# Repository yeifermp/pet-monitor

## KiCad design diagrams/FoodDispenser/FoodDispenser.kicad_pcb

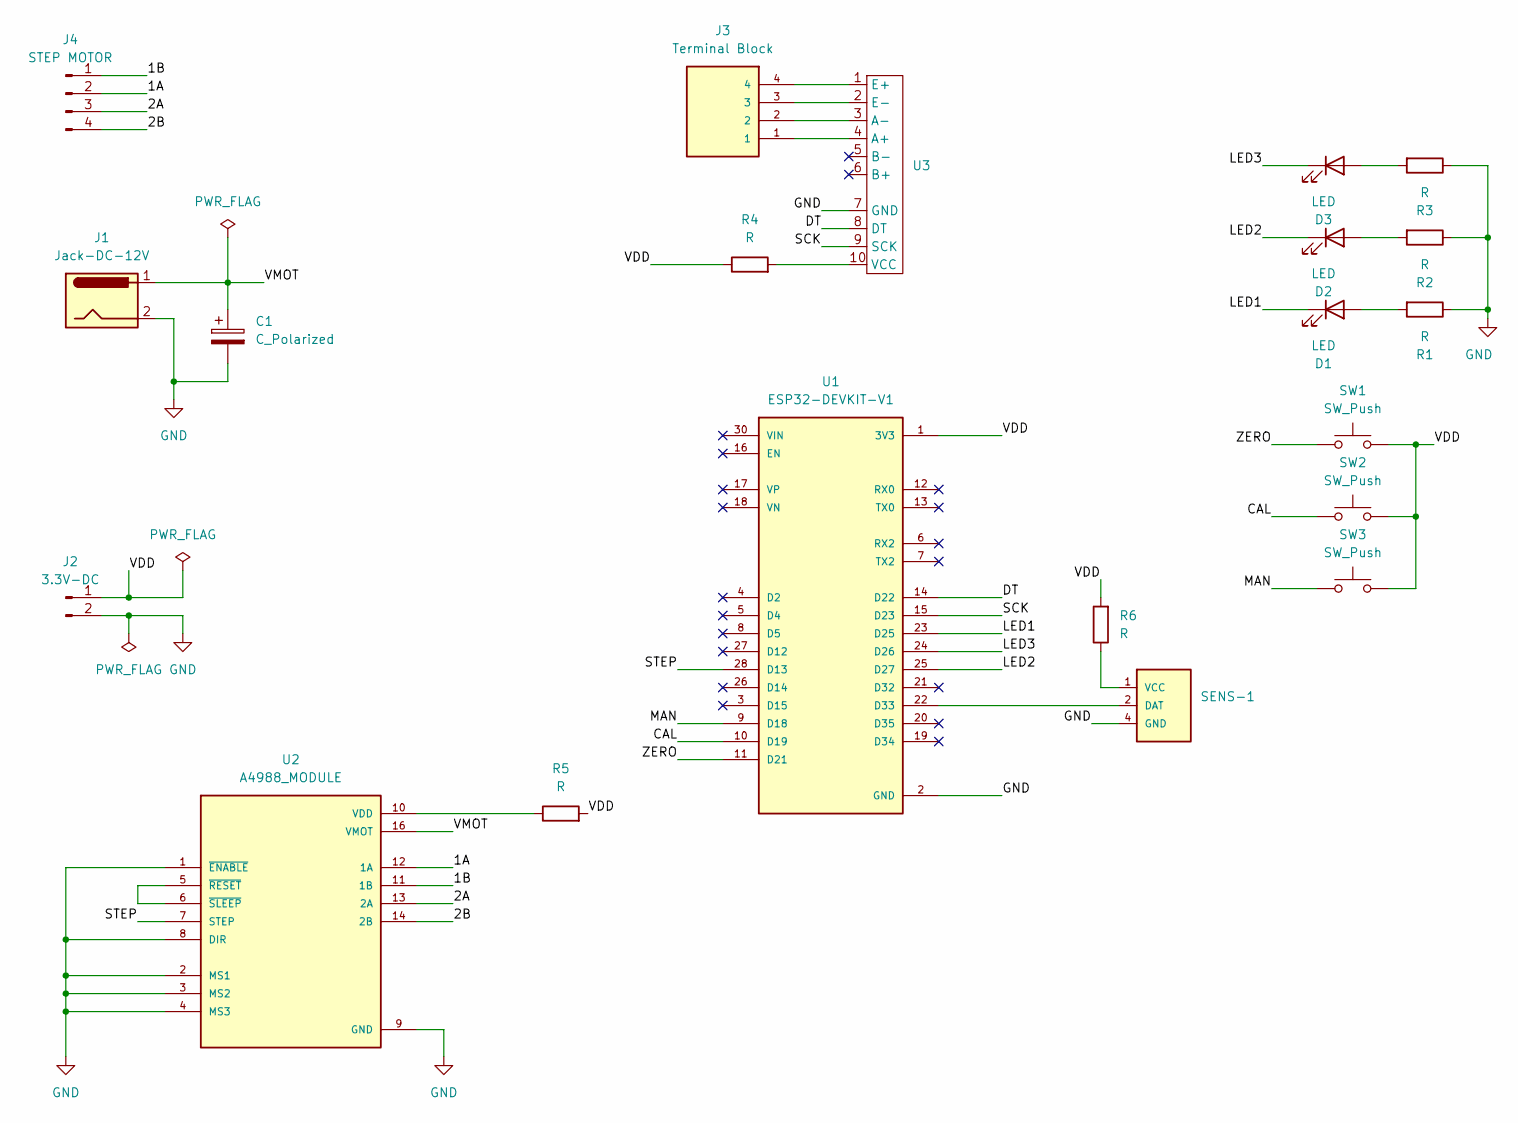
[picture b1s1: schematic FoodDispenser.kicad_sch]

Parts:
C1: C_Polarized; CP_Radial_D6.3mm_P2.50mm
D1, D2, D3: LED; LED_D3.0mm
J1: Jack-DC-12V; BarrelJack_Horizontal
J2: 3.3V-DC; PinHeader_1x02_P2.54mm_Vertical
J3: Terminal Block; Termial_Block_04
J4: STEP MOTOR; PinHeader_1x04_P2.54mm_Vertical
R1, R2, R3: R; R_Axial_DIN0207_L6.3mm_D2.5mm_P7.62mm_Horizontal
R4, R5, R6: R; R_1206_3216Metric_Pad1.30x1.75mm_HandSolder
SENS-1: SENSOR-DHT11
SW1, SW2, SW3: SW_Push; SW_PUSH-12mm
U1: ESP32-DEVKIT-V1; MODULE_ESP32_DEVKIT_V1; PARTREV N/A
U2: A4988_MODULE
U3: HX711-MODULE

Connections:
/1A: J4.2, U2.12 (1A)
/1B: J4.1, U2.11 (1B)
/2A: J4.3, U2.13 (2A)
/2B: J4.4, U2.14 (2B)
/CAL: SW2.1, U1.10 (D19)
/DT: U1.14 (D22), U3.8 (DT)
/LED1: D1.1 (K), U1.23 (D25)
/LED2: D2.1 (K), U1.25 (D27)
/LED3: D3.1 (K), U1.24 (D26)
/MAN: SW3.1, U1.9 (D18)
/SCK: U1.15 (D23), U3.9 (SCK)
/STEP: U1.28 (D13), U2.7 (STEP)
/VDD: J2.1, R4.1, R5.2, R6.2, SW1.2, SW2.2, SW3.2, U1.1 (3V3)
/VMOT: C1.1, J1.1, U2.16 (VMOT)
/ZERO: SW1.1, U1.11 (D21)
GND: C1.2, J1.2, J2.2, R1.1, R2.1, R3.1, SENS-1.4 (GND), U1.2 (GND), U1.29 (GND), U2.1 (~ENABLE), U2.2 (MS1), U2.3 (MS2), U2.4 (MS3), U2.8 (DIR), U2.9 (GND), U2.15 (GND), U3.7 (GND)
unnamed: D1.2 (A), R1.2
unnamed: D2.2 (A), R2.2
unnamed: D3.2 (A), R3.2
unnamed: SENS-1.2 (DAT), U1.22 (D33)
unnamed: R6.1, SENS-1.1 (VCC)
unnamed: R5.1, U2.10 (VDD)
unnamed: U2.5 (~RESET), U2.6 (~SLEEP)
unnamed: J3.1, U3.4 (A+)
unnamed: J3.2, U3.3 (A-)
unnamed: J3.4, U3.1 (E+)
unnamed: J3.3, U3.2 (E-)
unnamed: R4.2, U3.10 (VCC)

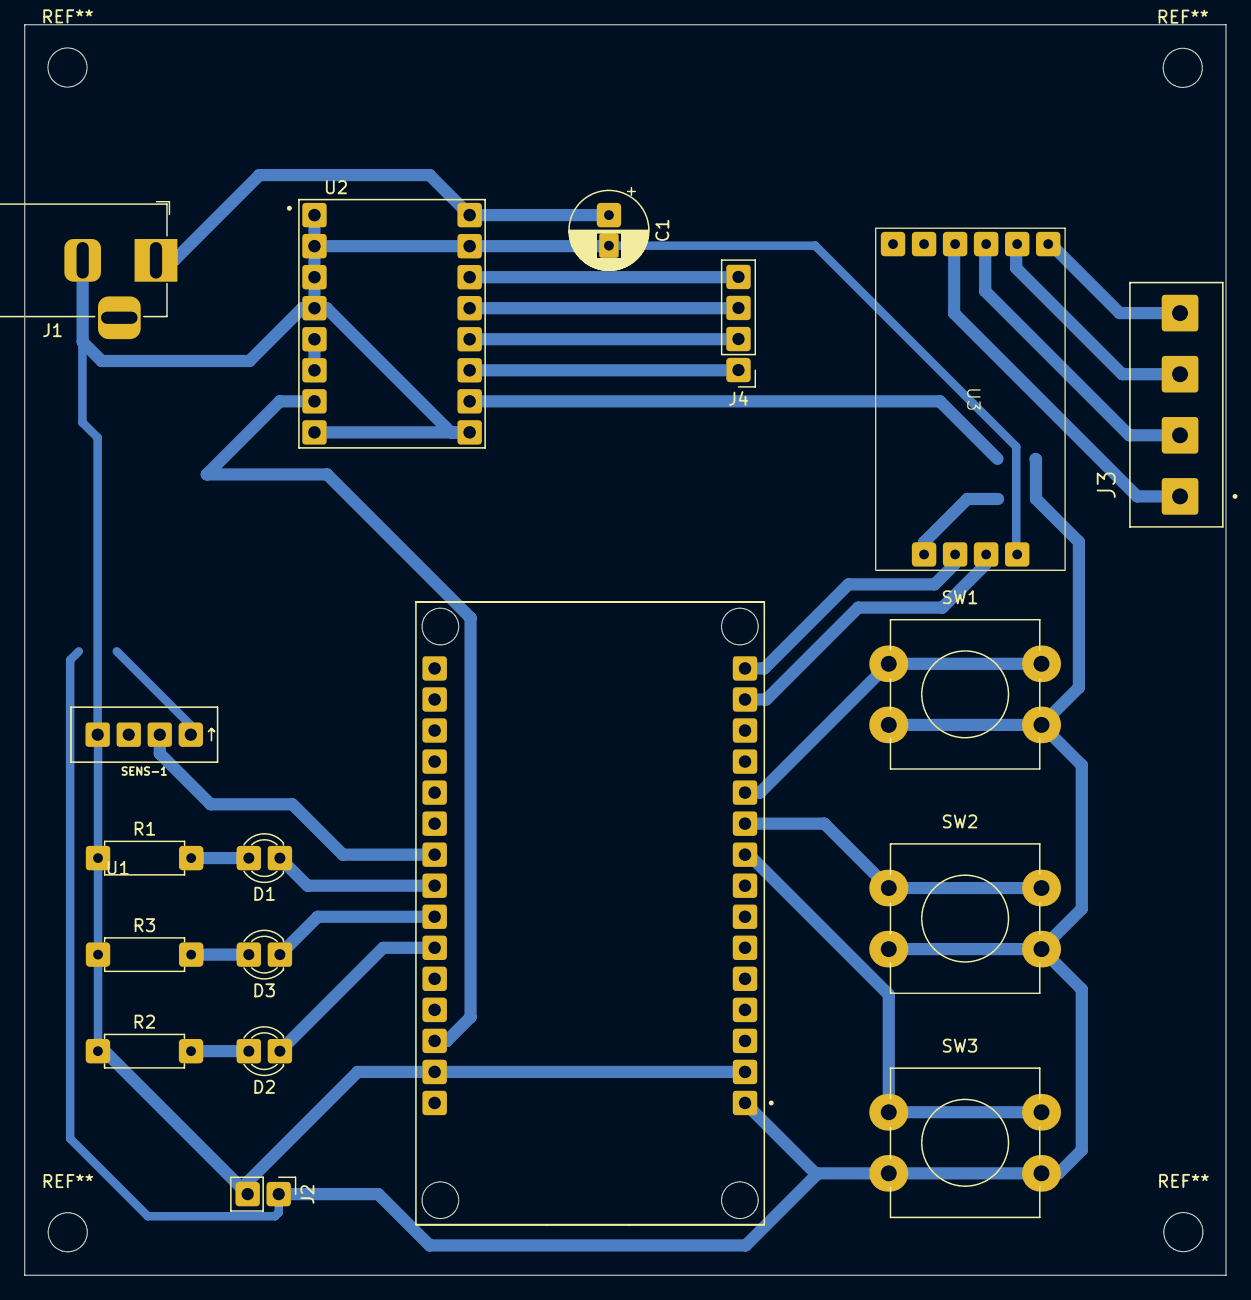
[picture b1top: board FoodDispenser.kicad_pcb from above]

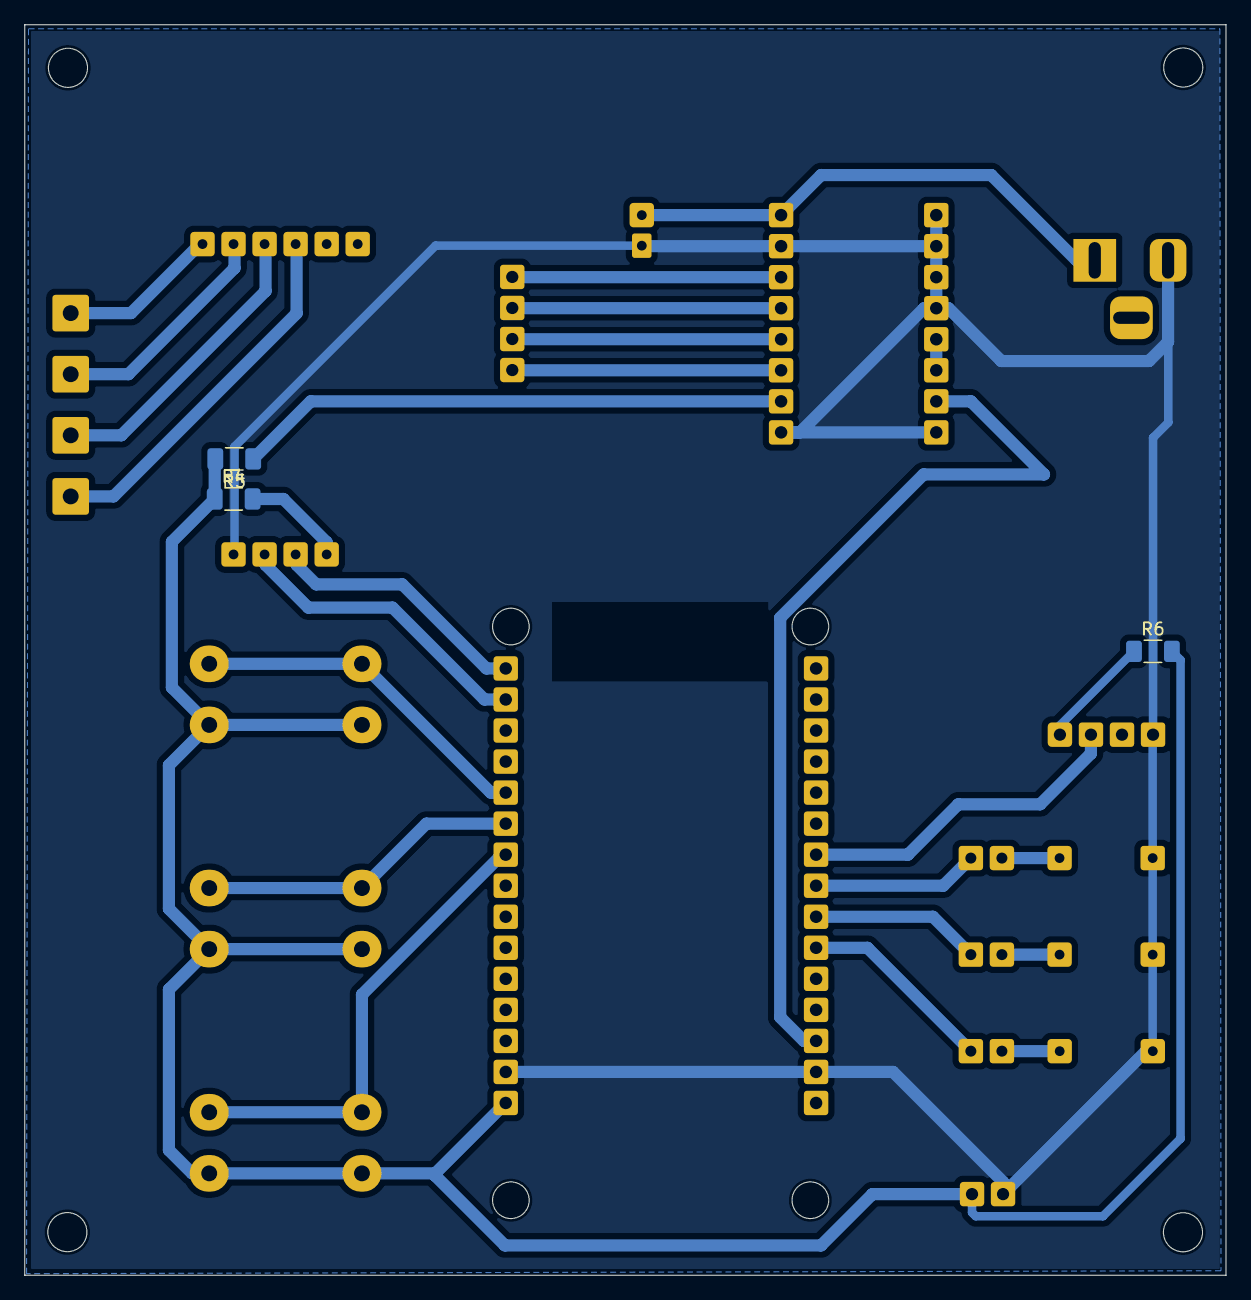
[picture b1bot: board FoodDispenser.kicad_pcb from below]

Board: 2 copper layers, 98.3 x 102.3 mm, 21 parts (3 on the bottom side), 28 nets.

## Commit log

2025-12-12 Include basic calibration
2025-12-12 Fixing an error
2026-01-07 Diagrams
2026-01-07 Upload baseline for Camera Module and Diagrams
